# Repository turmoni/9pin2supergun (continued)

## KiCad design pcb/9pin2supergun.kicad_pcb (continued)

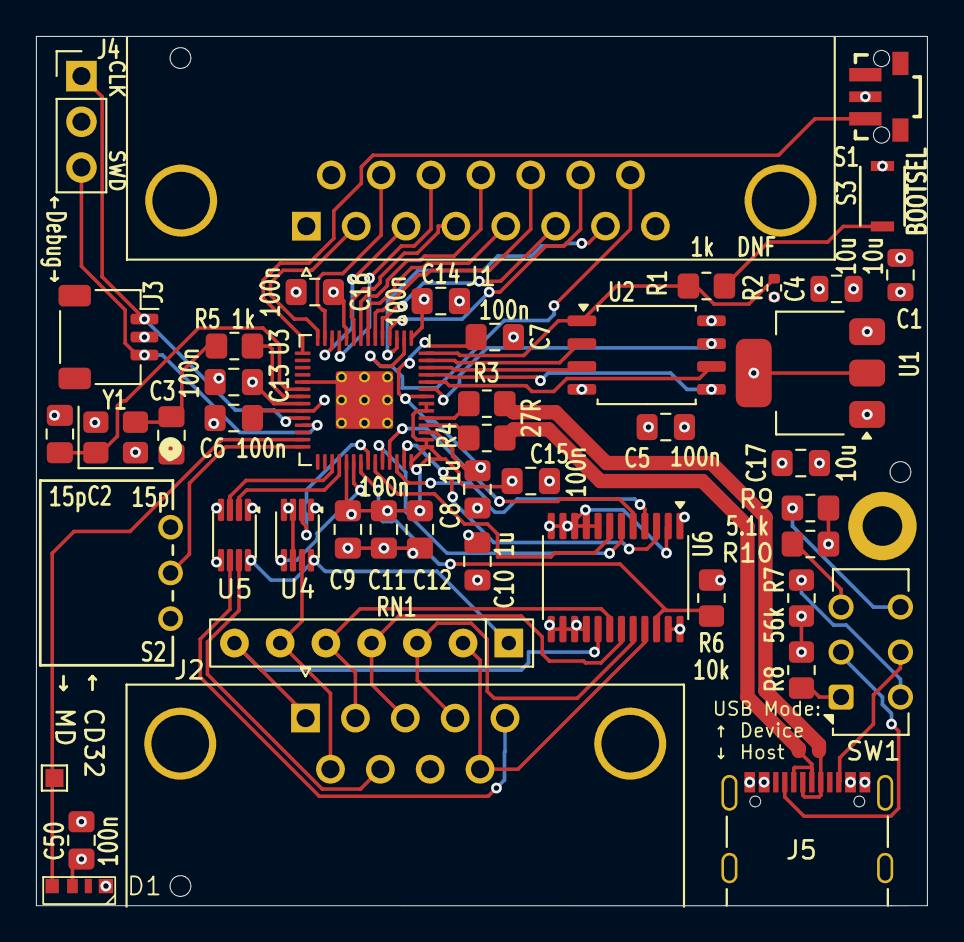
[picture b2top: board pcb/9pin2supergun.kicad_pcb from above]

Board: 4 copper layers, 49.5 x 48.3 mm, 47 parts (1 on the bottom side), 59 nets.

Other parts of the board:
QR*****: QR code

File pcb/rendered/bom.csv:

"Refs","Value","Footprint","Qty","DNP"
"C1","10u","Capacitor_SMD:C_0805_2012Metric","1",""
"C2","15p","Capacitor_SMD:C_0805_2012Metric_Pad1.18x1.45mm_HandSolder","1",""
"C3","15p","Capacitor_SMD:C_0805_2012Metric_Pad1.18x1.45mm_HandSolder","1",""
"C4","10u","Capacitor_SMD:C_0805_2012Metric","1",""
"C5","100n","Capacitor_SMD:C_0805_2012Metric_Pad1.18x1.45mm_HandSolder","1",""
"C6","100n","Capacitor_SMD:C_0805_2012Metric_Pad1.18x1.45mm_HandSolder","1",""
"C7","100n","Capacitor_SMD:C_0805_2012Metric_Pad1.18x1.45mm_HandSolder","1",""
"C8","1u","Capacitor_SMD:C_0805_2012Metric_Pad1.18x1.45mm_HandSolder","1",""
"C9","100n","Capacitor_SMD:C_0805_2012Metric_Pad1.18x1.45mm_HandSolder","1",""
"C10","1u","Capacitor_SMD:C_0805_2012Metric_Pad1.18x1.45mm_HandSolder","1",""
"C11","100n","Capacitor_SMD:C_0805_2012Metric_Pad1.18x1.45mm_HandSolder","1",""
"C12","100n","Capacitor_SMD:C_0805_2012Metric_Pad1.18x1.45mm_HandSolder","1",""
"C13","100n","Capacitor_SMD:C_0805_2012Metric_Pad1.18x1.45mm_HandSolder","1",""
"C14","100n","Capacitor_SMD:C_0805_2012Metric_Pad1.18x1.45mm_HandSolder","1",""
"C15","100n","Capacitor_SMD:C_0805_2012Metric_Pad1.18x1.45mm_HandSolder","1",""
"C16","100n","Capacitor_SMD:C_0805_2012Metric_Pad1.18x1.45mm_HandSolder","1",""
"C17","10u","Capacitor_SMD:C_0805_2012Metric_Pad1.18x1.45mm_HandSolder","1",""
"C50","100n","Capacitor_SMD:C_0805_2012Metric_Pad1.18x1.45mm_HandSolder","1",""
"D1","SK6812B","9pin2supergun:SK6812B","1",""
"J1","DA15_Receptacle","Connector_Dsub:DSUB-15_Female_Horizontal_P2.77x2.84mm_EdgePinOffset9.90mm_Housed_MountingHolesOffset11.32mm","1",""
"J2","Controller Input","Connector_Dsub:DSUB-9_Male_Horizontal_P2.77x2.84mm_EdgePinOffset7.70mm_Housed_MountingHolesOffset9.12mm","1",""
"J3","Debug (JST SH)","Connector_JST:JST_SH_SM03B-SRSS-TB_1x03-1MP_P1.00mm_Horizontal","1",""
"J4","Debug (2.54mm holes)","Connector_PinHeader_2.54mm:PinHeader_1x03_P2.54mm_Vertical","1",""
"J5","UJ20-C-H-C-4-SMT-TR","9pin2supergun:CUI_UJ20-C-H-C-4-SMT-TR","1",""
"R1","1k","Resistor_SMD:R_0805_2012Metric_Pad1.20x1.40mm_HandSolder","1",""
"R2","DNF","Resistor_SMD:R_0402_1005Metric","1",""
"R3","27R","Resistor_SMD:R_0805_2012Metric_Pad1.20x1.40mm_HandSolder","1",""
"R4","27R","Resistor_SMD:R_0805_2012Metric_Pad1.20x1.40mm_HandSolder","1",""
"R5","1k","Resistor_SMD:R_0805_2012Metric_Pad1.20x1.40mm_HandSolder","1",""
"R6","10k","Resistor_SMD:R_0805_2012Metric_Pad1.20x1.40mm_HandSolder","1",""
"R7","56k","Resistor_SMD:R_0805_2012Metric_Pad1.20x1.40mm_HandSolder","1",""
"R8","56k","Resistor_SMD:R_0805_2012Metric_Pad1.20x1.40mm_HandSolder","1",""
"RN1","10k","Resistor_THT:R_Array_SIP7","1",""
"S1","436333033816","9pin2supergun:436333033816","1",""
"S2","09.10201.02","footprints:SW3_09.10201.02_EAO","1",""
"S3","R-667995","9pin2supergun:R-667995_MIT","1",""
"U1","NCP1117-3.3_SOT223","Package_TO_SOT_SMD:SOT-223-3_TabPin2","1",""
"U2","W25Q128JVS","Package_SO:SOIC-8_5.23x5.23mm_P1.27mm","1",""
"U3","RP2040","MCU_RaspberryPi_and_Boards:RP2040-QFN-56","1",""
"U6","SN74LVC8T245","Package_SO:TSSOP-24_4.4x7.8mm_P0.65mm","1",""
"U7","SN74AVC4T245PW","Package_SO:TSSOP-16_4.4x5mm_P0.65mm","1",""
"Y1","ABM8-272-T3","Crystal:Crystal_SMD_3225-4Pin_3.2x2.5mm","1",""

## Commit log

2025-11-17 Support multiple pin sets, allowing for building for a Pi Pico or my PCB. This was a lot more work than it sounds.
2025-11-18 Readme updates, CD32 coin chord
2025-11-18 Add PCB
2025-11-18 Ignore some PCB files
2025-11-18 Clippy fixes
2025-11-18 Minor cleanups
2025-11-18 Add kicad rendering, hopefully working
2025-11-18 Add newline to try to kick off action
2025-11-18 Fix action, hopefully
2025-11-18 Give permissions?
2025-11-18 Render schematics and gerbers
2025-11-18 Update README having published the PCB
2025-11-19 Update from upstream template
2025-11-19 Disable current clippy complexity warnings - I don't think they're in places where fixing them would actually help all that much.
2025-11-19 Make clippy even happier
2025-11-19 See if this workflow works
2025-11-19 I do actually know what this pin does
2025-11-19 Fix config, hopefully
2025-11-19 Install udev?
2025-11-19 Absolute path?
2025-11-19 Oh the error was coming from elf2uf2. I hate the commits of shame involved with automation.
2025-11-19 Adding write permissions
2025-11-19 More README cleanups and more info
2025-11-19 Update the schematic to properly use hierarchical sheets, update the PCB to match, tidy up some weirdnesses (button with a "U" refdes, both S and SW refdes, etc)
2025-11-20 Add README for PCB, update automation, hopefully correctly
2025-11-20 Bump file to test automation
2025-11-20 I guess tags-ignore * is effectively ignoring everything?
2025-11-20 Clarify R2, move the top line above the images
2025-12-04 Add a reference Pico design
2025-12-04 Update KiCad rendering job to indicate it's only for the main PCB
2025-12-04 Add job to render the reference design
2025-12-04 Fix name and some parameters updated in error
2025-12-04 Add blank line to trigger render job
2025-12-04 Fix another missed replacement
2025-12-04 And remove the blank line
2026-01-07 Missed out the track from /OE to the actual chips that use it, which is unhelpful.
2026-01-07 And somehow the 3.3v also got disconnected there?
2026-01-07 And the DRC didn't tell me that coin wasn't connected either
2026-01-08 Documentation updates
2026-01-08 Clarify components
2026-01-10 It's not just for a Pi Pico any more
2026-02-05 Update PCB to v1.1: * Update level shifting to a component that actually supports 5V * Make both D-Sub connectors the same size in terms of pin offset (added bonus of making the board smaller) * Upda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
2026-02-06 Update Pico reference design to use different level shifters
2026-02-06 Add note about SW1
2026-02-06 Update for new level shifting
2026-02-06 Add note about changing a shifter for PCBA
2026-02-10 Replace framework with embassy-rp for future benefits
2026-02-10 Remove unused import
2026-02-10 We don't really need to waste energy building on multiple platforms
